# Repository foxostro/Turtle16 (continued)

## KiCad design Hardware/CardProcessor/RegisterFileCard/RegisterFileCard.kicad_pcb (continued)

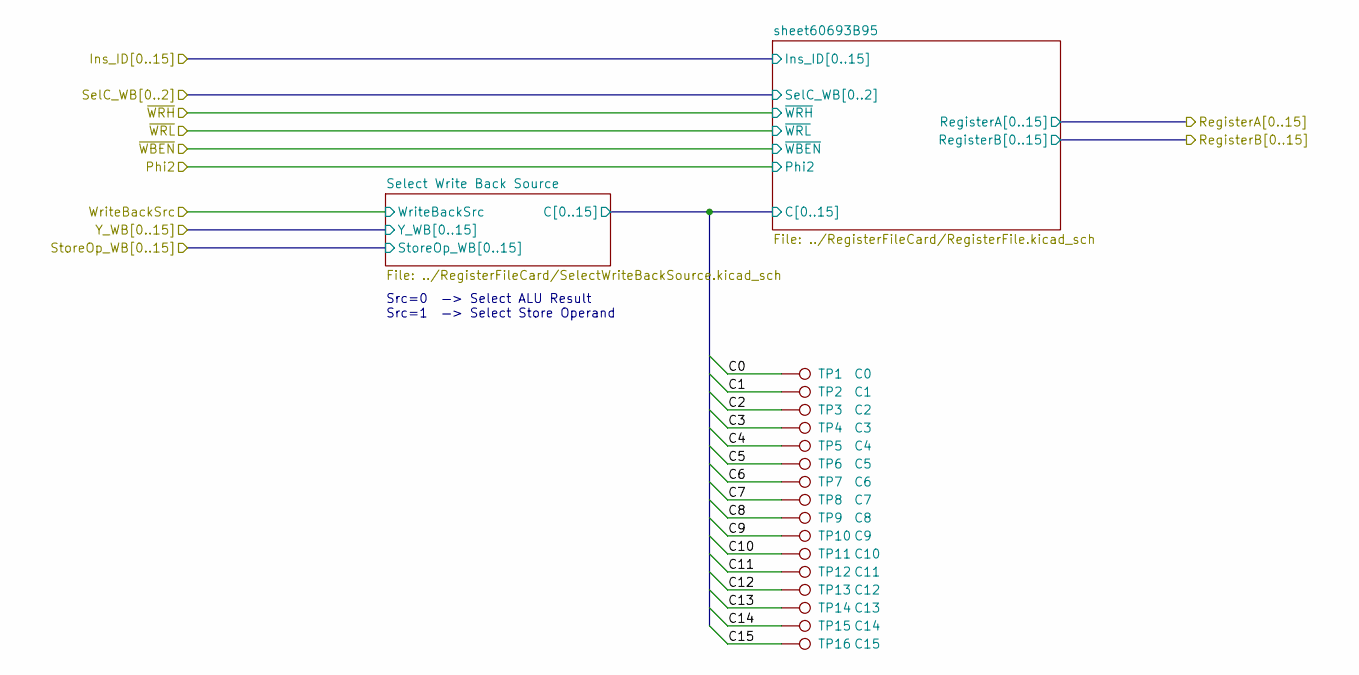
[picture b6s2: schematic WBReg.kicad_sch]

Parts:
TP1: C0; TestPoint_Pad_D1.0mm
TP2: C1; TestPoint_Pad_D1.0mm
TP3: C2; TestPoint_Pad_D1.0mm
TP4: C3; TestPoint_Pad_D1.0mm
TP5: C4; TestPoint_Pad_D1.0mm
TP6: C5; TestPoint_Pad_D1.0mm
TP7: C6; TestPoint_Pad_D1.0mm
TP8: C7; TestPoint_Pad_D1.0mm
TP9: C8; TestPoint_Pad_D1.0mm
TP10: C9; TestPoint_Pad_D1.0mm
TP11: C10; TestPoint_Pad_D1.0mm
TP12: C11; TestPoint_Pad_D1.0mm
TP13: C12; TestPoint_Pad_D1.0mm
TP14: C13; TestPoint_Pad_D1.0mm
TP15: C14; TestPoint_Pad_D1.0mm
TP16: C15; TestPoint_Pad_D1.0mm

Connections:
/Write Back and Register File/Select Write Back Source/C0: TP1.1; also elsewhere on the board
/Write Back and Register File/Select Write Back Source/C1: TP2.1; also elsewhere on the board
/Write Back and Register File/Select Write Back Source/C2: TP3.1; also elsewhere on the board
/Write Back and Register File/Select Write Back Source/C3: TP4.1; also elsewhere on the board
/Write Back and Register File/Select Write Back Source/C4: TP5.1; also elsewhere on the board
/Write Back and Register File/Select Write Back Source/C5: TP6.1; also elsewhere on the board
/Write Back and Register File/Select Write Back Source/C6: TP7.1; also elsewhere on the board
/Write Back and Register File/Select Write Back Source/C7: TP8.1; also elsewhere on the board
/Write Back and Register File/Select Write Back Source/C8: TP9.1; also elsewhere on the board
/Write Back and Register File/Select Write Back Source/C9: TP10.1; also elsewhere on the board
/Write Back and Register File/Select Write Back Source/C10: TP11.1; also elsewhere on the board
/Write Back and Register File/Select Write Back Source/C11: TP12.1; also elsewhere on the board
/Write Back and Register File/Select Write Back Source/C12: TP13.1; also elsewhere on the board
/Write Back and Register File/Select Write Back Source/C13: TP14.1; also elsewhere on the board
/Write Back and Register File/Select Write Back Source/C14: TP15.1; also elsewhere on the board
/Write Back and Register File/Select Write Back Source/C15: TP16.1; also elsewhere on the board

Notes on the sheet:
Src=0 —> Select ALU Result Src=1 —> Select Store Operand

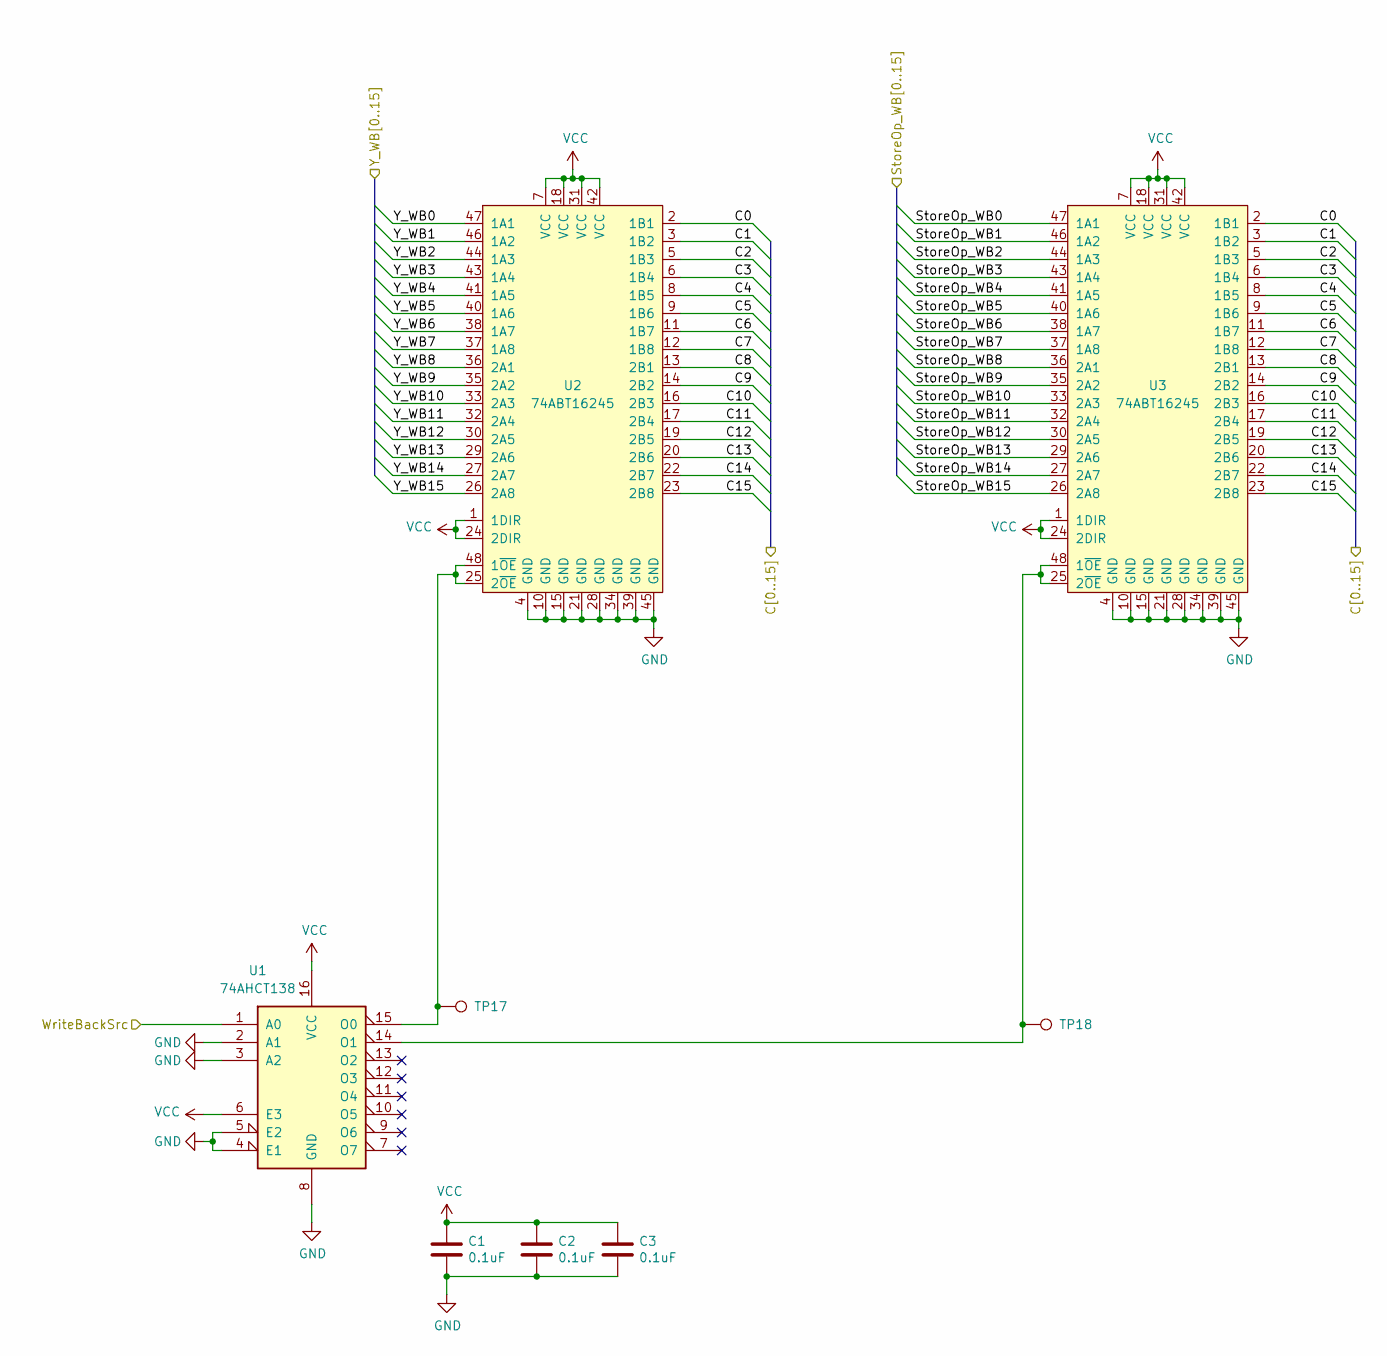
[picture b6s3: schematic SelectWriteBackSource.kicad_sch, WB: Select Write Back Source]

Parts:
C1, C2, C3: 0.1uF; C_0603_1608Metric; Manufacturer# EMK107B7104KAHT; Mouser# 963-EMK107B7104KAHT
TP17, TP18: TP; TestPoint_Pad_D1.0mm
U1: 74AHCT138; TSSOP-16_4.4x5mm_P0.65mm; Manufacturer# SN74AHCT138PWR; Mouser# 595-SN74AHCT138PWR
U2, U3: 74ABT16245; TSSOP-48_6.1x12.5mm_P0.5mm; Manufacturer# SN74ABTH16245DGGR; Mouser# 595-SNABTH16245DGGR

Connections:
/CardEdgeREG/StoreOp_WB0: U3.47 (1A1); also elsewhere on the board
/CardEdgeREG/StoreOp_WB1: U3.46 (1A2); also elsewhere on the board
/CardEdgeREG/StoreOp_WB2: U3.44 (1A3); also elsewhere on the board
/CardEdgeREG/StoreOp_WB3: U3.43 (1A4); also elsewhere on the board
/CardEdgeREG/StoreOp_WB4: U3.41 (1A5); also elsewhere on the board
/CardEdgeREG/StoreOp_WB5: U3.40 (1A6); also elsewhere on the board
/CardEdgeREG/StoreOp_WB6: U3.38 (1A7); also elsewhere on the board
/CardEdgeREG/StoreOp_WB7: U3.37 (1A8); also elsewhere on the board
/CardEdgeREG/StoreOp_WB8: U3.36 (2A1); also elsewhere on the board
/CardEdgeREG/StoreOp_WB9: U3.35 (2A2); also elsewhere on the board
/CardEdgeREG/StoreOp_WB10: U3.33 (2A3); also elsewhere on the board
/CardEdgeREG/StoreOp_WB11: U3.32 (2A4); also elsewhere on the board
/CardEdgeREG/StoreOp_WB12: U3.30 (2A5); also elsewhere on the board
/CardEdgeREG/StoreOp_WB13: U3.29 (2A6); also elsewhere on the board
/CardEdgeREG/StoreOp_WB14: U3.27 (2A7); also elsewhere on the board
/CardEdgeREG/StoreOp_WB15: U3.26 (2A8); also elsewhere on the board
/CardEdgeREG/WriteBackSrc: U1.1 (A0); also elsewhere on the board
/CardEdgeREG/Y_WB0: U2.47 (1A1); also elsewhere on the board
/CardEdgeREG/Y_WB1: U2.46 (1A2); also elsewhere on the board
/CardEdgeREG/Y_WB2: U2.44 (1A3); also elsewhere on the board
/CardEdgeREG/Y_WB3: U2.43 (1A4); also elsewhere on the board
/CardEdgeREG/Y_WB4: U2.41 (1A5); also elsewhere on the board
/CardEdgeREG/Y_WB5: U2.40 (1A6); also elsewhere on the board
/CardEdgeREG/Y_WB6: U2.38 (1A7); also elsewhere on the board
/CardEdgeREG/Y_WB7: U2.37 (1A8); also elsewhere on the board
/CardEdgeREG/Y_WB8: U2.36 (2A1); also elsewhere on the board
/CardEdgeREG/Y_WB9: U2.35 (2A2); also elsewhere on the board
/CardEdgeREG/Y_WB10: U2.33 (2A3); also elsewhere on the board
/CardEdgeREG/Y_WB11: U2.32 (2A4); also elsewhere on the board
/CardEdgeREG/Y_WB12: U2.30 (2A5); also elsewhere on the board
/CardEdgeREG/Y_WB13: U2.29 (2A6); also elsewhere on the board
/CardEdgeREG/Y_WB14: U2.27 (2A7); also elsewhere on the board
/CardEdgeREG/Y_WB15: U2.26 (2A8); also elsewhere on the board
/Write Back and Register File/Select Write Back Source/C0: U2.2 (1B1), U3.2 (1B1); also elsewhere on the board
/Write Back and Register File/Select Write Back Source/C1: U2.3 (1B2), U3.3 (1B2); also elsewhere on the board
/Write Back and Register File/Select Write Back Source/C2: U2.5 (1B3), U3.5 (1B3); also elsewhere on the board
/Write Back and Register File/Select Write Back Source/C3: U2.6 (1B4), U3.6 (1B4); also elsewhere on the board
/Write Back and Register File/Select Write Back Source/C4: U2.8 (1B5), U3.8 (1B5); also elsewhere on the board
/Write Back and Register File/Select Write Back Source/C5: U2.9 (1B6), U3.9 (1B6); also elsewhere on the board
/Write Back and Register File/Select Write Back Source/C6: U2.11 (1B7), U3.11 (1B7); also elsewhere on the board
/Write Back and Register File/Select Write Back Source/C7: U2.12 (1B8), U3.12 (1B8); also elsewhere on the board
/Write Back and Register File/Select Write Back Source/C8: U2.13 (2B1), U3.13 (2B1); also elsewhere on the board
/Write Back and Register File/Select Write Back Source/C9: U2.14 (2B2), U3.14 (2B2); also elsewhere on the board
/Write Back and Register File/Select Write Back Source/C10: U2.16 (2B3), U3.16 (2B3); also elsewhere on the board
/Write Back and Register File/Select Write Back Source/C11: U2.17 (2B4), U3.17 (2B4); also elsewhere on the board
/Write Back and Register File/Select Write Back Source/C12: U2.19 (2B5), U3.19 (2B5); also elsewhere on the board
/Write Back and Register File/Select Write Back Source/C13: U2.20 (2B6), U3.20 (2B6); also elsewhere on the board
/Write Back and Register File/Select Write Back Source/C14: U2.22 (2B7), U3.22 (2B7); also elsewhere on the board
/Write Back and Register File/Select Write Back Source/C15: U2.23 (2B8), U3.23 (2B8); also elsewhere on the board
GND: C1.2, C2.2, C3.2, U1.2 (A1), U1.3 (A2), U1.4 (E1), U1.5 (E2), U1.8 (GND), U2.4 (GND), U2.10 (GND), U2.15 (GND), U2.21 (GND), U2.28 (GND), U2.34 (GND), U2.39 (GND), U2.45 (GND), U3.4 (GND), U3.10 (GND), U3.15 (GND), U3.21 (GND), U3.28 (GND), U3.34 (GND), U3.39 (GND), U3.45 (GND); also elsewhere on the board
unnamed: TP17.1, U1.15 (O0), U2.25 (2~OE), U2.48 (1~OE)
unnamed: TP18.1, U1.14 (O1), U3.25 (2~OE), U3.48 (1~OE)
VCC: C1.1, C2.1, C3.1, U1.6 (E3), U1.16 (VCC), U2.1 (1DIR), U2.7 (VCC), U2.18 (VCC), U2.24 (2DIR), U2.31 (VCC), U2.42 (VCC), U3.1 (1DIR), U3.7 (VCC), U3.18 (VCC), U3.24 (2DIR), U3.31 (VCC), U3.42 (VCC); also elsewhere on the board

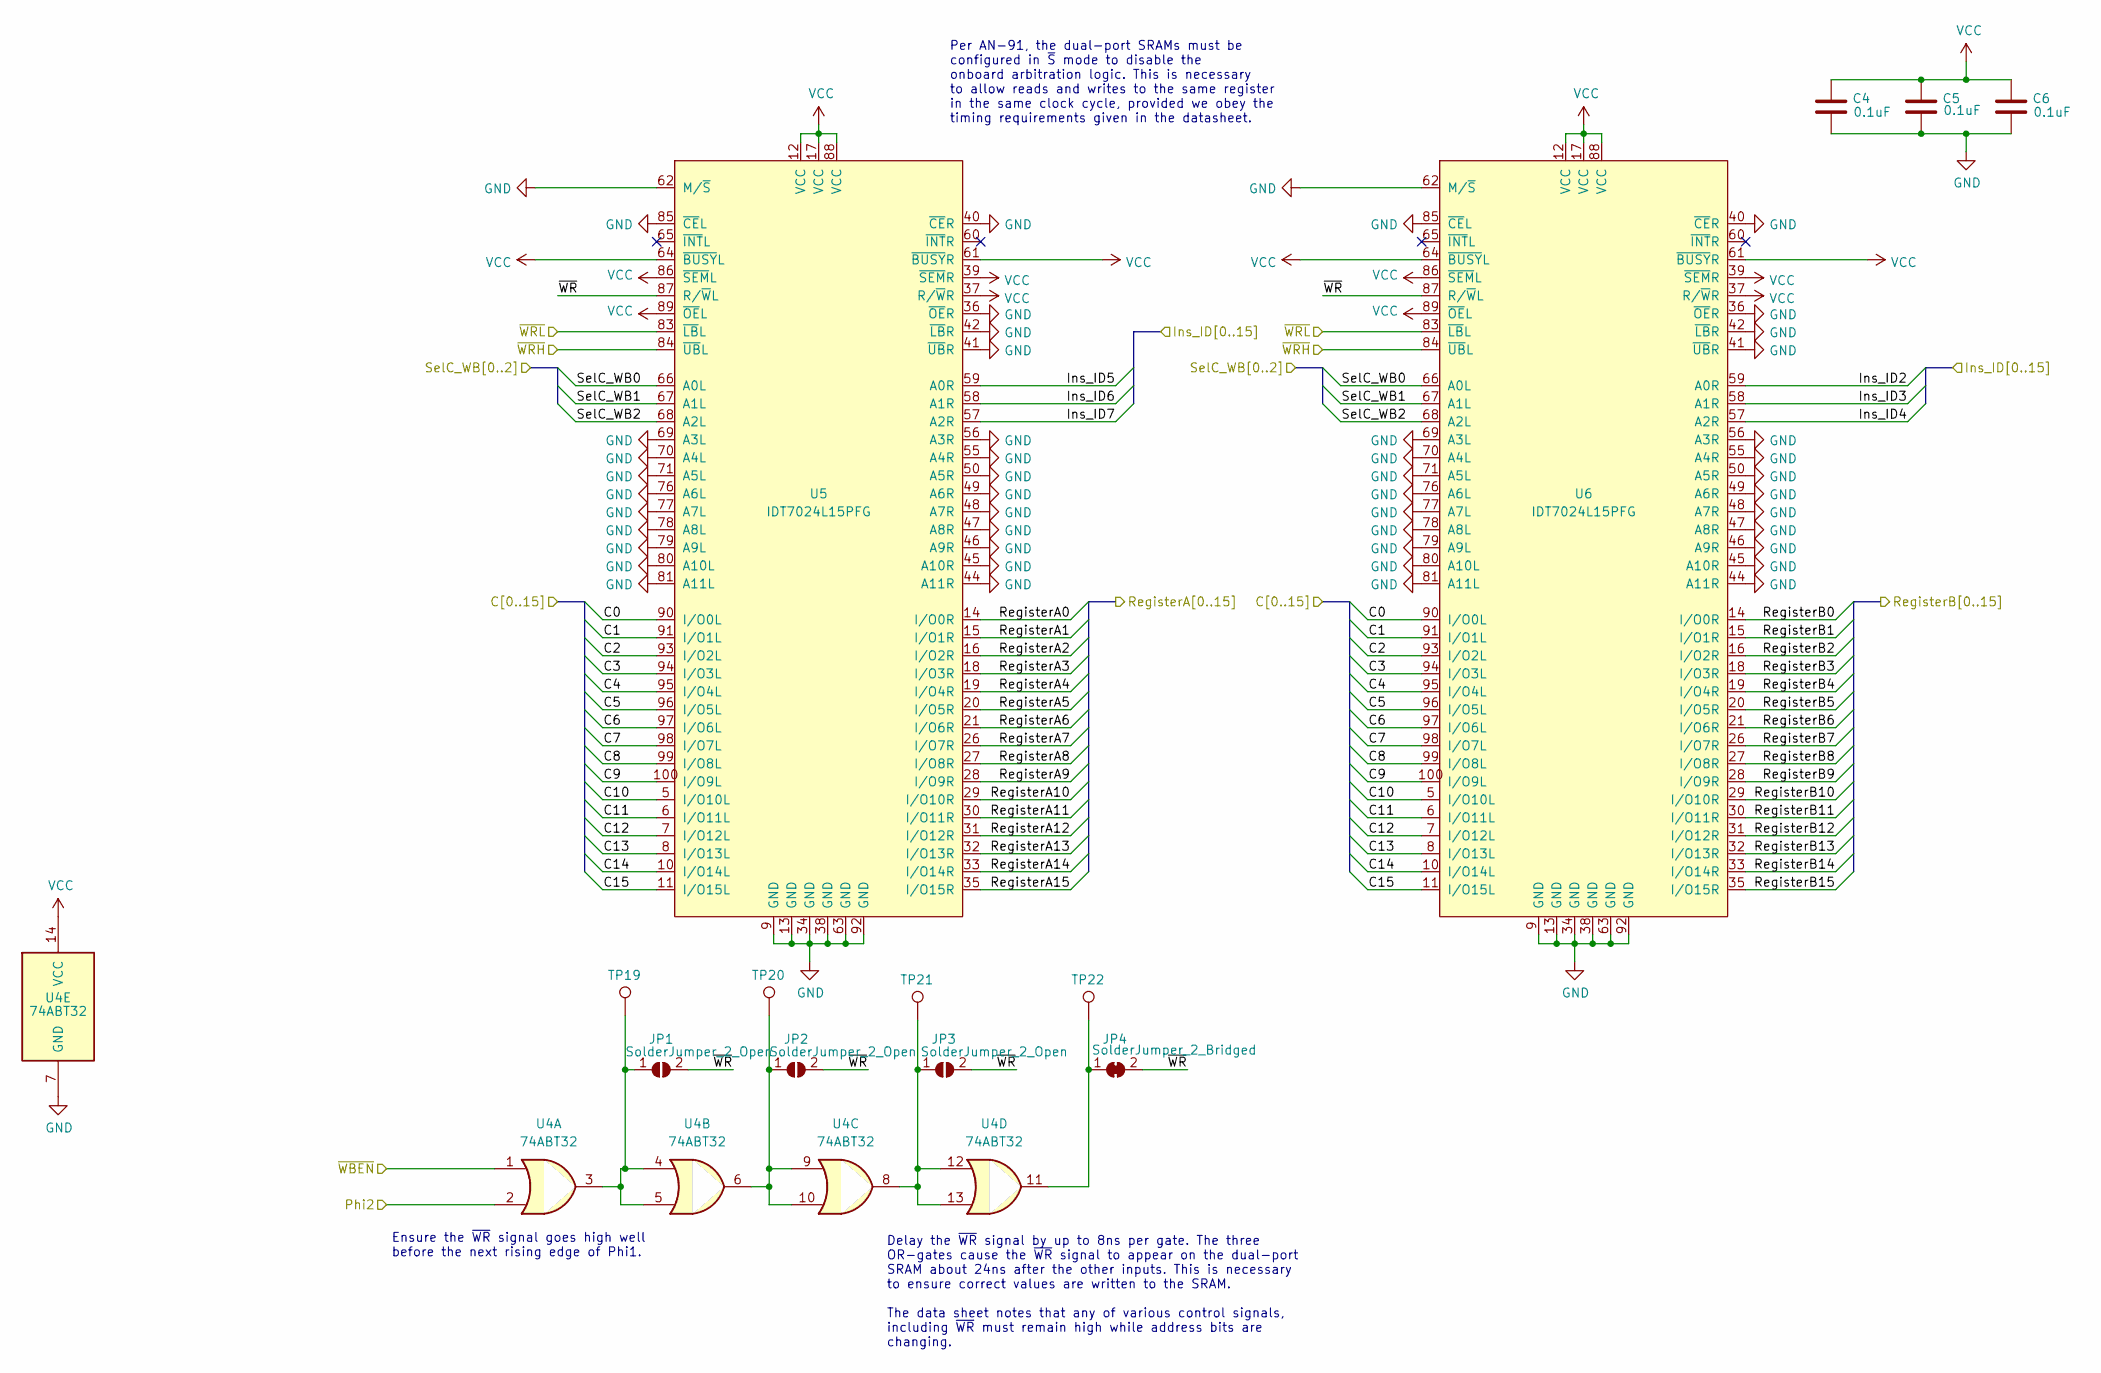
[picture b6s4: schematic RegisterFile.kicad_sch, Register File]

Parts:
C4, C5, C6: 0.1uF; C_0603_1608Metric; Manufacturer# EMK107B7104KAHT; Mouser# 963-EMK107B7104KAHT
JP1, JP2, JP3: SolderJumper_2_Open; SolderJumper-2_P1.3mm_Open_RoundedPad1.0x1.5mm
JP4: SolderJumper_2_Bridged; SolderJumper-2_P1.3mm_Bridged2Bar_RoundedPad1.0x1.5mm
TP19, TP20, TP21, TP22: TP; TestPoint_Pad_D1.0mm
U4: 74ABT32; TSSOP-14_4.4x5mm_P0.65mm; Manufacturer# 74ABT32PW,118; Mouser# 771-ABT32PW118
U5, U6: IDT7024L15PFG; TQFP-100_14x14mm_P0.5mm; Manufacturer# 7024L15PFG; Mouser# 972-7024L15PFG

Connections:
/CardEdgeREG/Ins_ID2: U6.59 (A0R); also elsewhere on the board
/CardEdgeREG/Ins_ID3: U6.58 (A1R); also elsewhere on the board
/CardEdgeREG/Ins_ID4: U6.57 (A2R); also elsewhere on the board
/CardEdgeREG/Ins_ID5: U5.59 (A0R); also elsewhere on the board
/CardEdgeREG/Ins_ID6: U5.58 (A1R); also elsewhere on the board
/CardEdgeREG/Ins_ID7: U5.57 (A2R); also elsewhere on the board
/CardEdgeREG/Phi2: U4.2; also elsewhere on the board
/CardEdgeREG/RegisterA0: U5.14 (I/O0R); also elsewhere on the board
/CardEdgeREG/RegisterA1: U5.15 (I/O1R); also elsewhere on the board
/CardEdgeREG/RegisterA2: U5.16 (I/O2R); also elsewhere on the board
/CardEdgeREG/RegisterA3: U5.18 (I/O3R); also elsewhere on the board
/CardEdgeREG/RegisterA4: U5.19 (I/O4R); also elsewhere on the board
/CardEdgeREG/RegisterA5: U5.20 (I/O5R); also elsewhere on the board
/CardEdgeREG/RegisterA6: U5.21 (I/O6R); also elsewhere on the board
/CardEdgeREG/RegisterA7: U5.26 (I/O7R); also elsewhere on the board
/CardEdgeREG/RegisterA8: U5.27 (I/O8R); also elsewhere on the board
/CardEdgeREG/RegisterA9: U5.28 (I/O9R); also elsewhere on the board
/CardEdgeREG/RegisterA10: U5.29 (I/O10R); also elsewhere on the board
/CardEdgeREG/RegisterA11: U5.30 (I/O11R); also elsewhere on the board
/CardEdgeREG/RegisterA12: U5.31 (I/O12R); also elsewhere on the board
/CardEdgeREG/RegisterA13: U5.32 (I/O13R); also elsewhere on the board
/CardEdgeREG/RegisterA14: U5.33 (I/O14R); also elsewhere on the board
/CardEdgeREG/RegisterA15: U5.35 (I/O15R); also elsewhere on the board
/CardEdgeREG/RegisterB0: U6.14 (I/O0R); also elsewhere on the board
/CardEdgeREG/RegisterB1: U6.15 (I/O1R); also elsewhere on the board
/CardEdgeREG/RegisterB2: U6.16 (I/O2R); also elsewhere on the board
/CardEdgeREG/RegisterB3: U6.18 (I/O3R); also elsewhere on the board
/CardEdgeREG/RegisterB4: U6.19 (I/O4R); also elsewhere on the board
/CardEdgeREG/RegisterB5: U6.20 (I/O5R); also elsewhere on the board
/CardEdgeREG/RegisterB6: U6.21 (I/O6R); also elsewhere on the board
/CardEdgeREG/RegisterB7: U6.26 (I/O7R); also elsewhere on the board
/CardEdgeREG/RegisterB8: U6.27 (I/O8R); also elsewhere on the board
/CardEdgeREG/RegisterB9: U6.28 (I/O9R); also elsewhere on the board
/CardEdgeREG/RegisterB10: U6.29 (I/O10R); also elsewhere on the board
/CardEdgeREG/RegisterB11: U6.30 (I/O11R); also elsewhere on the board
/CardEdgeREG/RegisterB12: U6.31 (I/O12R); also elsewhere on the board
/CardEdgeREG/RegisterB13: U6.32 (I/O13R); also elsewhere on the board
/CardEdgeREG/RegisterB14: U6.33 (I/O14R); also elsewhere on the board
/CardEdgeREG/RegisterB15: U6.35 (I/O15R); also elsewhere on the board
/CardEdgeREG/SelC_WB0: U5.66 (A0L), U6.66 (A0L); also elsewhere on the board
/CardEdgeREG/SelC_WB1: U5.67 (A1L), U6.67 (A1L); also elsewhere on the board
/CardEdgeREG/SelC_WB2: U5.68 (A2L), U6.68 (A2L); also elsewhere on the board
/CardEdgeREG/~WBEN: U4.1; also elsewhere on the board
/CardEdgeREG/~WRH: U5.84 (~UBL), U6.84 (~UBL); also elsewhere on the board
/CardEdgeREG/~WRL: U5.83 (~LBL), U6.83 (~LBL); also elsewhere on the board
/Write Back and Register File/Select Write Back Source/C0: U5.90 (I/O0L), U6.90 (I/O0L); also elsewhere on the board
/Write Back and Register File/Select Write Back Source/C1: U5.91 (I/O1L), U6.91 (I/O1L); also elsewhere on the board
/Write Back and Register File/Select Write Back Source/C2: U5.93 (I/O2L), U6.93 (I/O2L); also elsewhere on the board
/Write Back and Register File/Select Write Back Source/C3: U5.94 (I/O3L), U6.94 (I/O3L); also elsewhere on the board
/Write Back and Register File/Select Write Back Source/C4: U5.95 (I/O4L), U6.95 (I/O4L); also elsewhere on the board
/Write Back and Register File/Select Write Back Source/C5: U5.96 (I/O5L), U6.96 (I/O5L); also elsewhere on the board
/Write Back and Register File/Select Write Back Source/C6: U5.97 (I/O6L), U6.97 (I/O6L); also elsewhere on the board
/Write Back and Register File/Select Write Back Source/C7: U5.98 (I/O7L), U6.98 (I/O7L); also elsewhere on the board
/Write Back and Register File/Select Write Back Source/C8: U5.99 (I/O8L), U6.99 (I/O8L); also elsewhere on the board
/Write Back and Register File/Select Write Back Source/C9: U5.100 (I/O9L), U6.100 (I/O9L); also elsewhere on the board
/Write Back and Register File/Select Write Back Source/C10: U5.5 (I/O10L), U6.5 (I/O10L); also elsewhere on the board
/Write Back and Register File/Select Write Back Source/C11: U5.6 (I/O11L), U6.6 (I/O11L); also elsewhere on the board
/Write Back and Register File/Select Write Back Source/C12: U5.7 (I/O12L), U6.7 (I/O12L); also elsewhere on the board
/Write Back and Register File/Select Write Back Source/C13: U5.8 (I/O13L), U6.8 (I/O13L); also elsewhere on the board
/Write Back and Register File/Select Write Back Source/C14: U5.10 (I/O14L), U6.10 (I/O14L); also elsewhere on the board
/Write Back and Register File/Select Write Back Source/C15: U5.11 (I/O15L), U6.11 (I/O15L); also elsewhere on the board
/Write Back and Register File/sheet60693B95/~WR: JP1.2 (B), JP2.2 (B), JP3.2 (B), JP4.2 (B), U5.87 (R/~WL), U6.87 (R/~WL)
GND: C4.2, C5.2, C6.2, U4.7 (GND), U5.9 (GND), U5.13 (GND), U5.34 (GND), U5.36 (~OER), U5.38 (GND), U5.40 (~CER), U5.41 (~UBR), U5.42 (~LBR), U5.44 (A11R), U5.45 (A10R), U5.46 (A9R), U5.47 (A8R), U5.48 (A7R), U5.49 (A6R), U5.50 (A5R), U5.55 (A4R), U5.56 (A3R), U5.62 (M/~S), U5.63 (GND), U5.69 (A3L), U5.70 (A4L), U5.71 (A5L), U5.76 (A6L), U5.77 (A7L), U5.78 (A8L), U5.79 (A9L), U5.80 (A10L), U5.81 (A11L), U5.85 (~CEL), U5.92 (GND), U6.9 (GND), U6.13 (GND), U6.34 (GND), U6.36 (~OER), U6.38 (GND), U6.40 (~CER), U6.41 (~UBR), U6.42 (~LBR), U6.44 (A11R), U6.45 (A10R), U6.46 (A9R), U6.47 (A8R), U6.48 (A7R), U6.49 (A6R), U6.50 (A5R), U6.55 (A4R), U6.56 (A3R), U6.62 (M/~S), U6.63 (GND), U6.69 (A3L), U6.70 (A4L), U6.71 (A5L), U6.76 (A6L), U6.77 (A7L), U6.78 (A8L), U6.79 (A9L), U6.80 (A10L), U6.81 (A11L), U6.85 (~CEL), U6.92 (GND); also elsewhere on the board
unnamed: JP1.1 (A), TP19.1, U4.3, U4.4, U4.5
unnamed: JP2.1 (A), TP20.1, U4.6, U4.9, U4.10
unnamed: JP3.1 (A), TP21.1, U4.8, U4.12, U4.13
unnamed: JP4.1 (A), TP22.1, U4.11
VCC: C4.1, C5.1, C6.1, U4.14 (VCC), U5.12 (VCC), U5.17 (VCC), U5.37 (R/~WR), U5.39 (~SEMR), U5.61 (~BUSYR), U5.64 (~BUSYL), U5.86 (~SEML), U5.88 (VCC), U5.89 (~OEL), U6.12 (VCC), U6.17 (VCC), U6.37 (R/~WR), U6.39 (~SEMR), U6.61 (~BUSYR), U6.64 (~BUSYL), U6.86 (~SEML), U6.88 (VCC), U6.89 (~OEL); also elsewhere on the board

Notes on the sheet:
Delay the ~{WR} signal by up to 8ns per gate. The three OR-gates cause the ~{WR} signal to appear on the dual-port SRAM about 24ns after the other inputs. This is necessary to ensure correct values are written to the SRAM. The data sheet notes that any of various control signals, including ~{WR} mu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
Per AN-91, the dual-port SRAMs must be configured in ~{S} mode to disable the onboard arbitration logic. This is necessary to allow reads and writes to the same register in the same clock cycle, provided we obey the timing requirements given in the datasheet.
Ensure the ~{WR} signal goes high well before the next rising edge of Phi1.

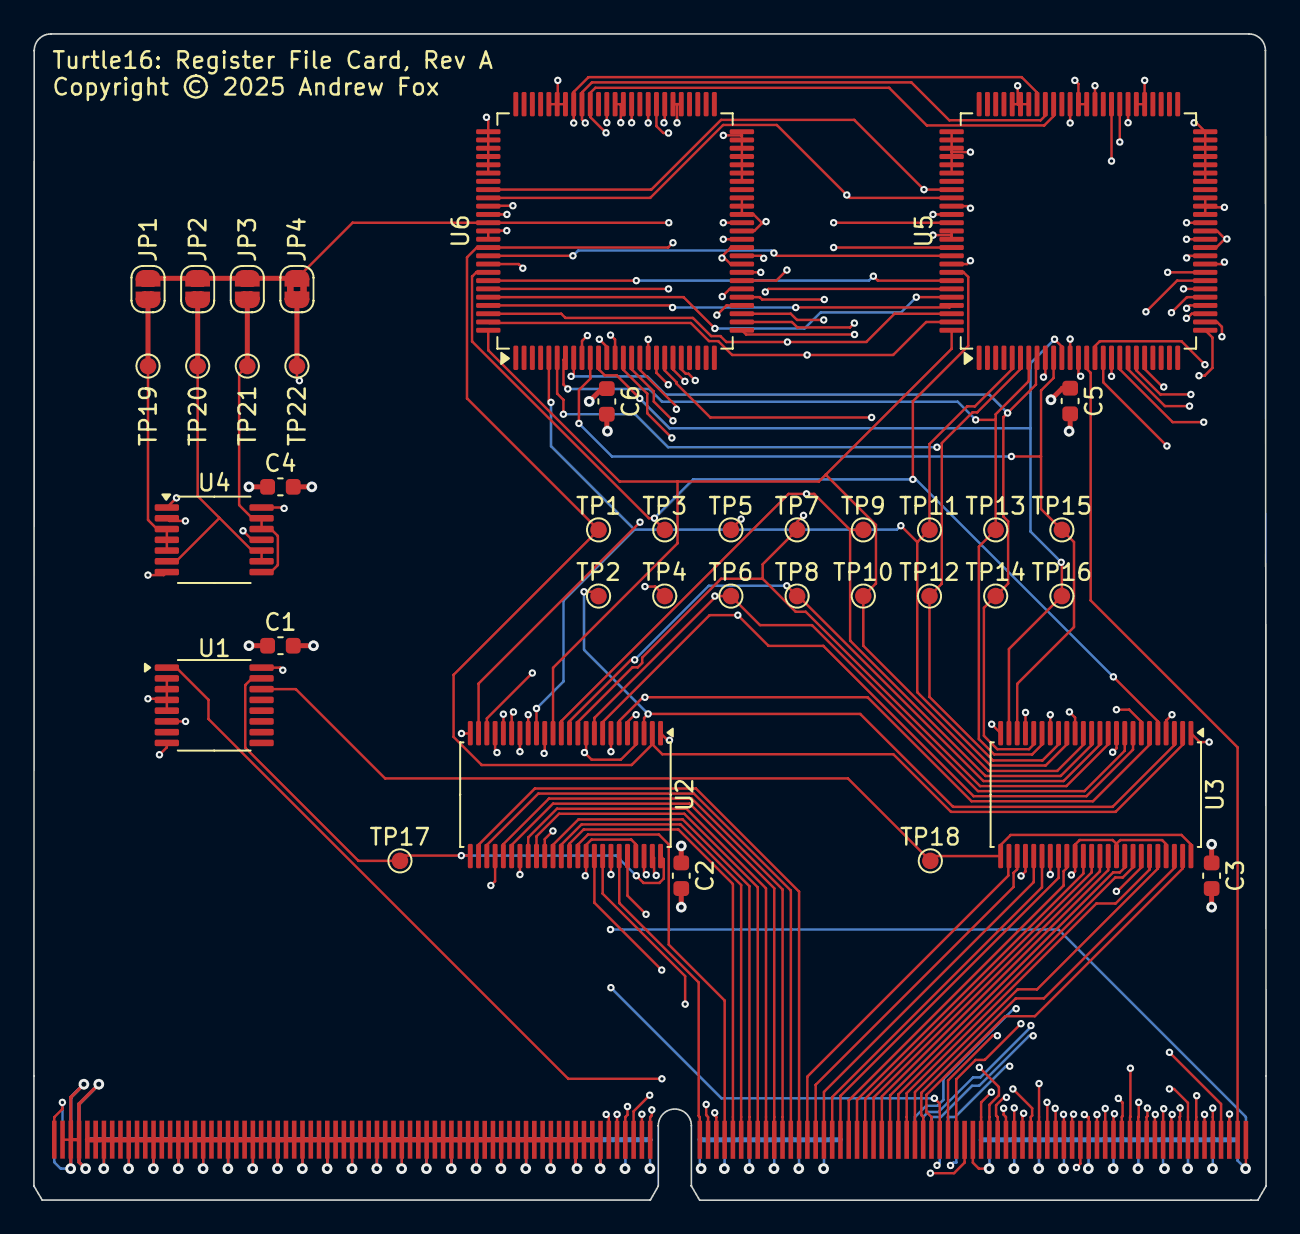
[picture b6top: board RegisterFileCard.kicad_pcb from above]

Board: 6 copper layers, 74.5 x 70.5 mm, 39 parts (0 on the bottom side), 103 nets.

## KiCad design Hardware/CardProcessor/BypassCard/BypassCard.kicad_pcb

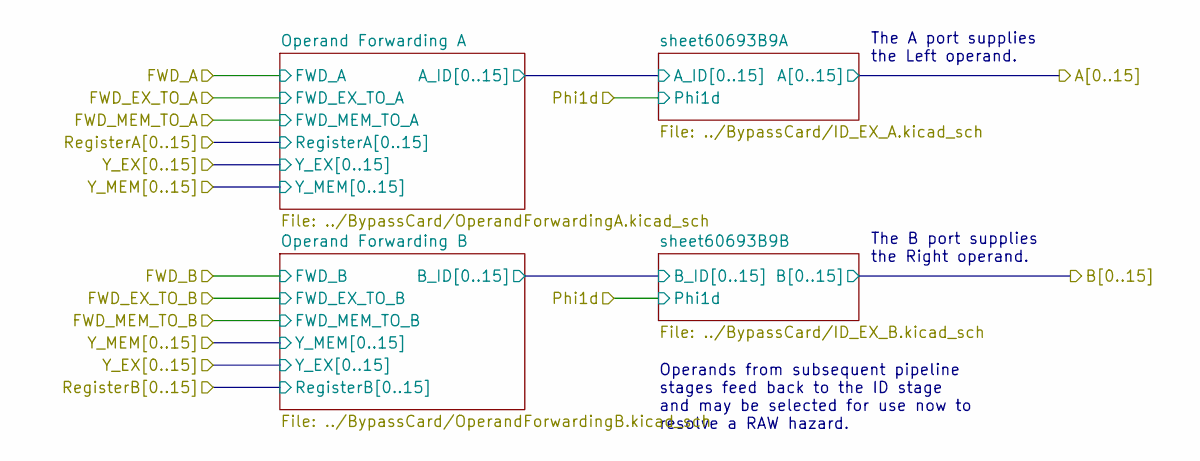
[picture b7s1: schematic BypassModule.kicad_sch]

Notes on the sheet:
The A port supplies the Left operand.
The B port supplies the Right operand.
Operands from subsequent pipeline stages feed back to the ID stage and may be selected for use now to resolve a RAW hazard.

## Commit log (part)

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2025-02-14 LiveInterval: style and comment
2025-02-14 RegisterLiveIntervalCalculator is now a struct and not an NSObject
2025-02-14 SnapCompilerMetrics is now an enum instead of an NSObject
2025-02-14 SnapSubcompilerFunctionDeclaration is now a struct instead of an NSObject
2025-02-14 Rename SnapSubcompilerStructDeclarationTests to StructScannerTests
2025-02-14 StructMemberFunctionCallMatcher is now a struct instead of an NSObject
2025-02-14 TackVirtualMachine no longer derives from NSObject
2025-02-14 SnapToTurtle16Compiler is now a struct instead of an NSObject
2025-02-14 CompilerPass no longer derives from NSObject
2025-02-14 AssemblerCommandLineDriver no longer derives from NSObject
2025-02-14 HazardControl no longer derives from NSObject
2025-02-15 SourceLineRangeMapper is now a struct instead of an NSObject
2025-02-15 AbstractSyntaxTreeNode and subclasses no longer derive from NSObject
2025-02-15 Subclasses of Expression are no longer nested in Expression
    This signficantly improves code readability by making it unnecessary to
    type "Expression." over and over again.
2025-02-16 Mark several Expression subclasses as "final"
2025-02-17 CompilerPassGenerics: wrap a few long lines of source code
2025-02-18 Env: style, comments, spacing, and indentation
2025-02-20 TraitDeclarationn description is indented now
2025-02-23 Rename SnapASTTransformerTestDeclaration to CompilerPassTestDeclaration
2025-04-29 SymbolStorage embeds the offset for cases which have one
2025-05-01 Add new registerStorage case to SymbolStorage
    This will be used for symbols which are bound directly to a register
    without being materialized in memory.
2025-05-01 Add a swift-format config file in TurtleTools/
2025-05-01 Code style and indentation
2025-05-01 Code style, avoiding long lines
2025-05-01 Add new Tack MOVE-type instructions
    Typed MOVE-type instructions will be useful for shuffling values between
    registers while evaluating expressions.
2025-05-01 CoreToTackCompiler: Choose bindings for symbols with register storage
    If attempting to assign a value to a symbol with register storage, but the
    symbol has no register binding, then the compiler will pick the next
    available register and bind that register to the symbol.
2025-05-04 Eseq is now a sequence of statements and one final expression
2025-05-10 CompilerPassEraseEseq: erases Eseq expressions
    The CompilerPassEraseEseq compiler pass will bubble the statements
    attached to an Eseq up the AST, toward the root, and replace the Eseq
    itself with the expression it bears.
2025-05-11 CompilerPass: evaluate the name of the trait in a type context
2025-05-11 CompilerPass: No need to set the context at all when we evaluate a PrimitiveType
2025-05-11 CompilerPassDecomposeExpressionsTests: add test assigning a struct value
    Add a new test, testAssignmentExpression_RightHandSideIsStructType, which
    demonstrates that assignment of non-primitive, non-POD types decomposes as
    expected.
2025-05-18 DecomposeExpr: decompose Subscript expressions
2025-06-03 Remove force-downcast from CompilerPass.visit(eseq:)
    This is another case where it really does seem like the Swift compiler
    is compiling force-downcast incorrectly. I find that a Seq may be erased
    during "flattening" if it has one child, replaced by the child. In this
    case, visit(seq:) may not return a Seq. My expectation is that a line
    like `visit(seq: foo) as! Seq` would cause a runtime error when this
    happens. However, this is not so. The compiler instead passes an invalid
2025-06-03 CompilerPassEraseUnions: no longer necessary to write parameter name, memoryLayoutStrategy
2025-06-09 Add methods to SymbolType to unwrap a union type
2025-06-09 CompilerPassLowerVarDecl: simplify TypeOf expressions where possible
    Simplify the type expression where we can obviously avoid a TypeOf
    expression. This avoids issues where the argument to TypeOf no longer
    type checks after various lowering steps have been applied. We do not
    necessarily want to lower the argument to TypeOf itself, though, as this
    may introduce temporary variables in a context which is only evaluated
    at compile-time.
2025-06-13 SymbolType: when lifting a struct/trait type, prefer to resolve as an Identifier naming the struct/trait
2025-06-13 CompilerPassEraseUnions: Need to bitcast the address of the payload to a pointer type
2025-06-29 Move files related to the monolithic processor design to a new MonolithicProcessor/ subdirectory
2025-06-30 Ensure all ProcessorBoard schematics use USLetter pages
2025-07-01 Add a MEC5-140-01-L-DV-W1-K to the board as a test
2025-07-05 Extract ID to new ControlModule sheet
2025-07-05 Reannotate schematic by hand since extracting to new sheets broke existing annotations
2025-07-05 Split net Phi1a into Phi1a and Phi1e
2025-07-05 Replace EXModule with a connector to a separate PCB
2025-07-05 Replace Bypass module with a connector to a separate PCB
2025-07-05 Resize ground plane
2025-07-05 EXModule: place components on PCB
2025-07-05 Add a keepout zone to prevent PCB traces and vias in the area which will be chamfered
2025-07-06 EXModule: Fix broken symlink to Turtle16.kicad_sym
2025-07-06 MainBoard: move the peripheral slots to the right-hand side of the board
2025-07-12 MainBoard: switch to six layer PCB because I think I do not need more
2025-07-12 MainBoard: the main board PCB is mostly routed now, but many ground pins are unconnected
2025-07-12 EXModule: update pinout of the card edge to match corresponding recent MainBoard changes
2025-07-12 EXModule: space out components more on the PCB
    Freerouting cannot find a good solution for the PCB with the old placement.
    Give more space between the bottom row of ICs and the card edge connector
    to make it easier to route signals through the connector.
2025-07-12 EXModule: remove the via keepout along the bottom edge
2025-07-13 MainBoard: more changes to the PCB route, and fix broken labels on clock test points
2025-07-17 CardEdgeTest: route the six layer PCB
2025-07-20 CardEdgeTest: generate Gerbers for manufacturing
2025-07-22 Rename RegisterFileModule to RegisterFileCard
2025-07-22 Rename PCIFModule to PCIFCard
2025-07-23 Annotate schematics such that Turtle16Computer can perform ERC and DRC
    - Turtle16Computer must be fully annotated to perform ERC on the schematic.
    Also, the PCB cannot be updated without full annotations either. However,
    KiCad projects for individual PCBs must also remain annotated and capable
    of updating the PCB and performing ERC and DRC.
    - Manually set KiCad project fields to "" in kicad_sch files
    - Manually replace the UUID of EXCard so it no longer collides with the
2025-07-29 Ensure all cards have a unique 4-bit identifier code and proper power pins
    The pinout on all cards will devote the first four pins to the identifier,
    followed by four pins for +5V, and four pins for GND. This allows a card to
    draw up to about 2 amps.
2025-07-29 EXCard: We want more vias to ground on the grounded card edge pins
2025-07-29 MEMCard: add zero ohm resistors to allow series termination of memory control signals, if needed
2025-07-31 MainBoard: ensure board outline matches dimensions of PCB cards
    The left side of the card, from the center of the keyway to the left edge,
    is exactly 72.000 mm. The right side of the card, from the center of the
    keyway to the right edge, is 72.025 mm. Adjust the outline of the main
    board PCB so the edge of the cards will exactly meet the edge of the main
    board.
2025-08-01 CardTestFixture: add new test fixture project, but PCB is not routed yet
2025-08-01 Adjust board outline and remove unnecessary I/O expander ICs
2025-08-01 CardTestFixture: change the six layer stackup to add another internal signal layer.
2025-08-30 No need to keep the Gerber files in the Git repo directly. We have the zip archive.
2025-09-09 exposeImplicitConversions() handles implicit conversion in assignments
2025-09-10 decomposeExpressions() attempts to incur less memory traffic
2025-09-10 Fix bug in `lift` which causes a lifted const pointer to always have a mutable pointee
2025-09-10 decomposeExpressions: emit VarDeclarations that have already been lowered
2025-09-11 Update Xcode project to recommended settings. This re-enables the module verifier.
2025-09-12 Add new compiler pass eraseCompileTimeExpressions()
    This pass will erase expressions which can be evaluated at compile time,
    such as compile time arithmetic, compile time boolean expression, Is,
    TypeOf, and SizeOf.
2025-09-12 CoreToTackCompiler: remove support for unions and traits
2025-09-12 CoreToTackCompiler: remove support for compile time arithmetic expressions
    Compile-time arithmetic expressions should have been erased in an earlier
    compiler pass. Remove support for them from CoreToTackCompiler.
2025-09-13 Consider any variable to be a compiler temporary if it starts with the reserved prefix, "__"
2025-09-13 exposeImplicitConversions: expose the implicit conversion from dynamic array to pointer which may occur in the object of a Get expression
2025-09-13 decomposeExpressions: special handing of subscripts with arguments that are literal ranges
2025-09-13 decomposeExpressions: testSubscriptArgumentOfLiteralRangeMustBePreserved
2025-09-13 Remove fragile testSimpleProgram and testFunctionDefinition tests
    We should test behavior, not the exact assembly listing of the program.
    This makes these tests fragile. The functionality covered by these tests
    is also already covered by such behavioral tests.
2025-09-13 ifPass: fix bug where dies on type checking an Eseq with variables
    If we check the Eseq before those variables are added to the environment
    then the type checker will throw an error for an unknown identifier.
2025-09-13 eraseEseq: add an option to ignore Eseq in a while-loop condition expr
    We cannot erase Eseq in a while-loop condition expr. Even so, we some
    times do want to erase all the other Eseq in the program that we can.
2025-09-14 Remove testRvalue_convert_pointer_to_trait unit test
    This test assumes the structure of the AST after compilation, which
    makes it very fragile. This functionality is best handled through
    behavioral integration tests in SnapCompilerFrontEndTests.
2025-09-18 withSymbol uses a mutable inout Symbol parameter
2025-09-18 Symbol now carries a set of Facts, including InitStatus
    Nothing updates or uses this fact yet.
2025-09-18 Add Expression.isPointee convenience method to identify "pointee"
2025-09-18 Add E2E integration tests to exercise rules about assignment and const
    The compiler will reject an assignment to a const variable when the
    compiler knows that variable to have already been initialized.
    The compiler will accept assignments to a const variable when the
    compiler knows that the variable has not been initialized yet.
2025-09-20 Add VarDeclaration.withMutable()
2025-09-20 Add TypeRecord.withType() and .withVisibility() builder methods
2025-09-20 Add Env.eraseConst()
    This method rewrites symbols & types in the environment to erase const
2025-09-20 Sort the files in the Xcode side bar again
2025-09-20 update Xcode project to reccommended settings for the new Xcode
2025-09-20 CompilerPassForIn: replace TypeOf(MutableType) with MutableType(TypeOf)
    The previous order is incorrect. MutableType is only meaningful in a
    type context, and TypeOf evaluates its expression in a value context.
    TypeOf gets the type of the value that the expression would yield.
2025-09-20 Turn on the typeCheck() pass
2025-09-21 wip checkpoint: trying to remove the `none` evaluation context
2025-09-22 Rename SnapSubcompilerIf to IfLowerer
2025-09-24 Rename SnapSubcompilerSubroutine to CompilerPassSubroutine
2025-09-24 Remove LvalueExpressionTypeChecker and replace all remaining useage of it
2025-09-24 added new benchmarking script, scripts/benchmark_protocol.sh
2025-10-31 Always sign with the Developer ID
2025-11-01 Add --no-runtime command line option to disable including the runtime
2025-11-01 Fix bug where compiler failed to compile runtime bounds checks for array accessed via pointer
2025-11-02 Add Examples/test_all_shifts.snap to test shift operations
